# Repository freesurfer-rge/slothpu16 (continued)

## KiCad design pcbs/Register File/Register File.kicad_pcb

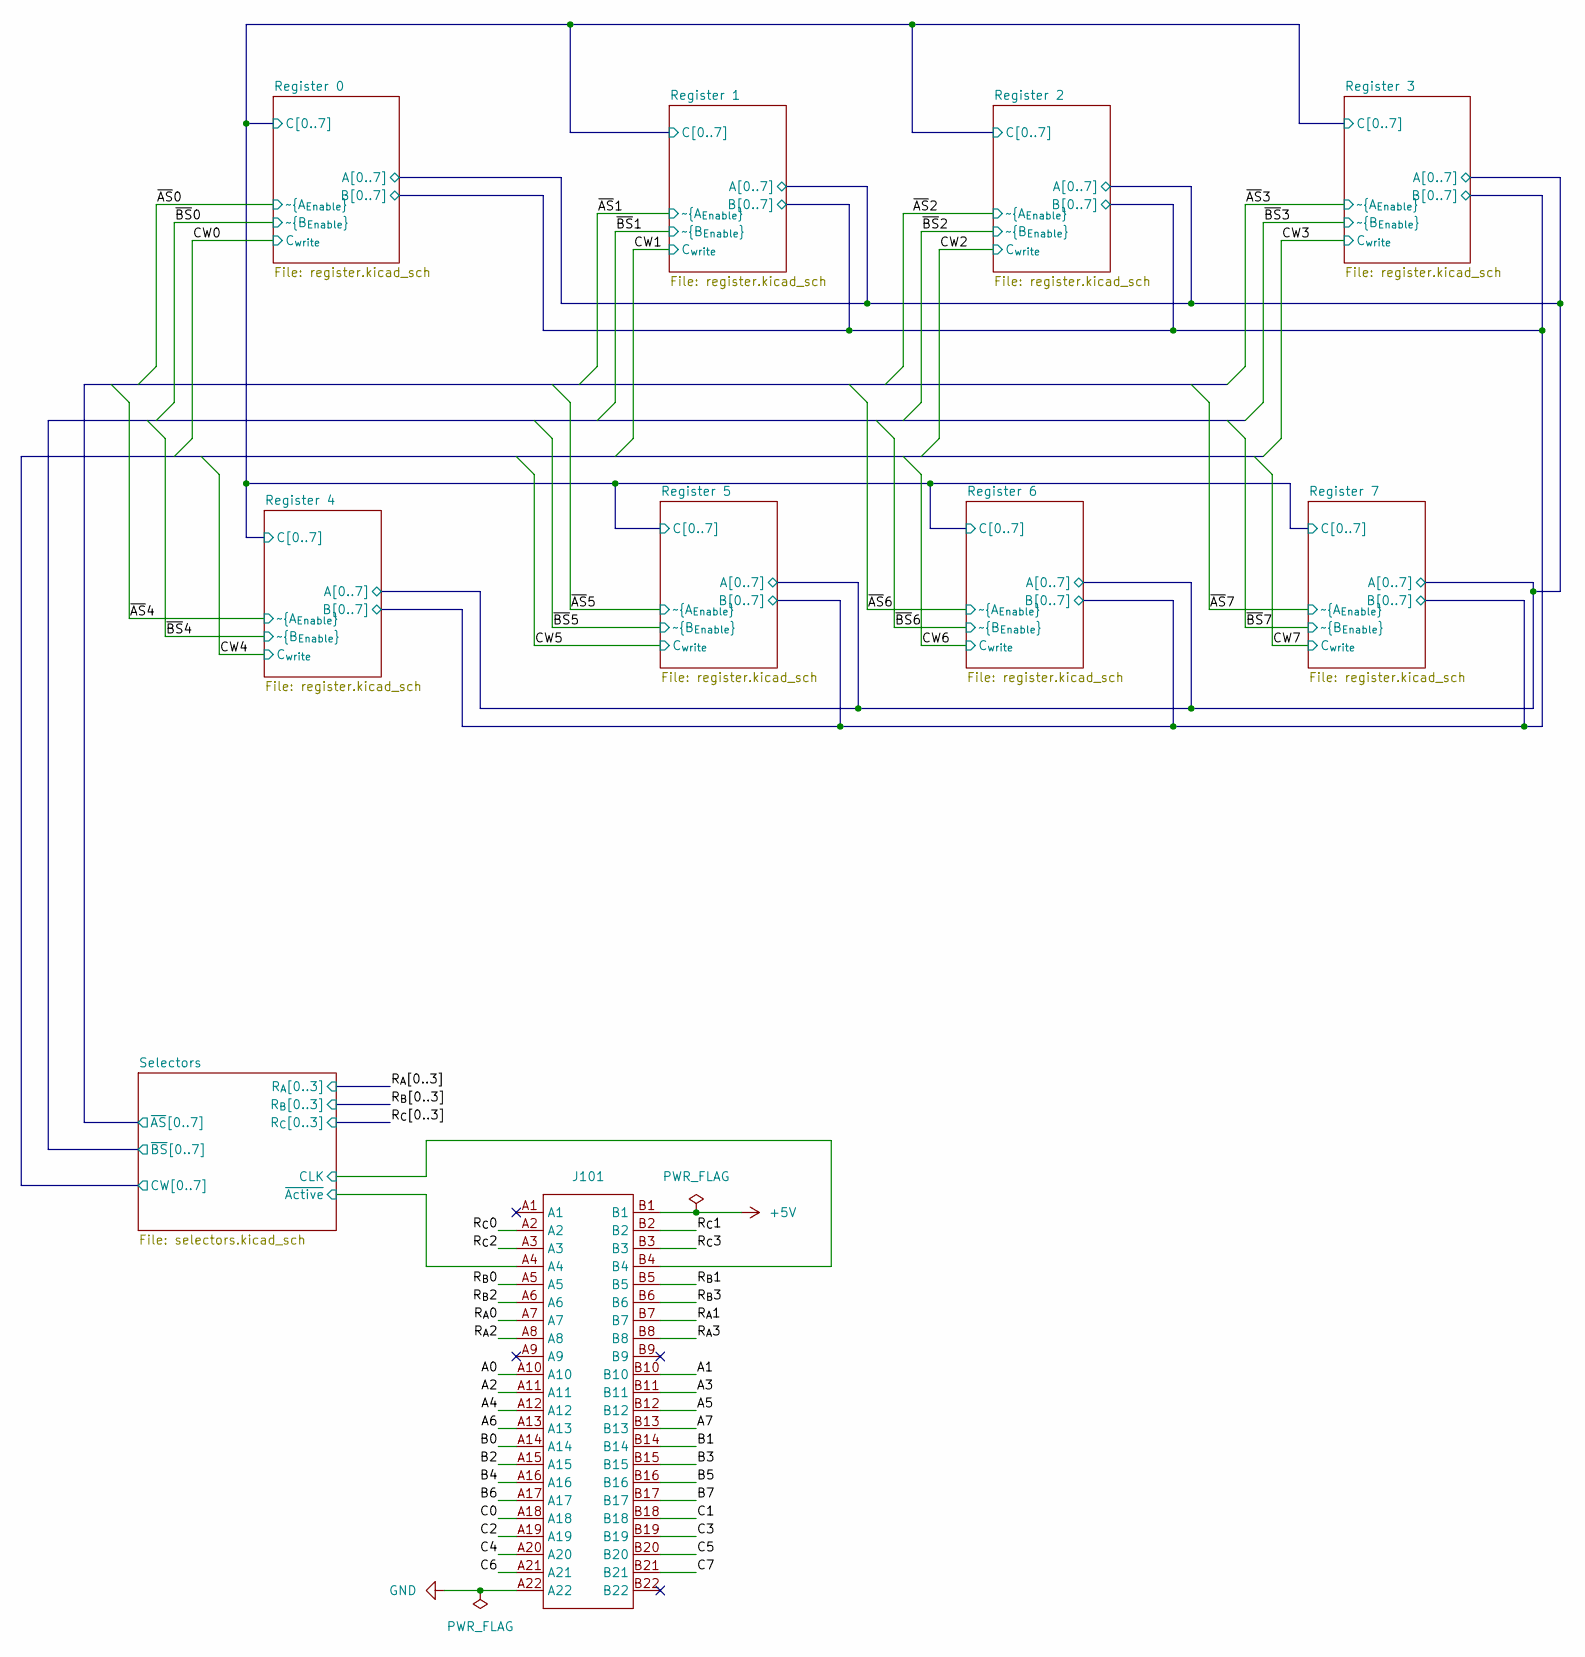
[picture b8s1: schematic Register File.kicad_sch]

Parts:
J101: TE-5530843-4-Edge

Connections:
+5V: J101.B1; also elsewhere on the board
/R_{A}0: J101.A7; also elsewhere on the board
/R_{A}1: J101.B7; also elsewhere on the board
/R_{A}2: J101.A8; also elsewhere on the board
/R_{A}3: J101.B8; also elsewhere on the board
/R_{B}0: J101.A5; also elsewhere on the board
/R_{B}1: J101.B5; also elsewhere on the board
/R_{B}2: J101.A6; also elsewhere on the board
/R_{B}3: J101.B6; also elsewhere on the board
/R_{C}0: J101.A2; also elsewhere on the board
/R_{C}1: J101.B2; also elsewhere on the board
/R_{C}2: J101.A3; also elsewhere on the board
/R_{C}3: J101.B3; also elsewhere on the board
/Register 0/A0: J101.A10; also elsewhere on the board
/Register 0/A1: J101.B10; also elsewhere on the board
/Register 0/A2: J101.A11; also elsewhere on the board
/Register 0/A3: J101.B11; also elsewhere on the board
/Register 0/A4: J101.A12; also elsewhere on the board
/Register 0/A5: J101.B12; also elsewhere on the board
/Register 0/A6: J101.A13; also elsewhere on the board
/Register 0/A7: J101.B13; also elsewhere on the board
/Register 0/B0: J101.A14; also elsewhere on the board
/Register 0/B1: J101.B14; also elsewhere on the board
/Register 0/B2: J101.A15; also elsewhere on the board
/Register 0/B3: J101.B15; also elsewhere on the board
/Register 0/B4: J101.A16; also elsewhere on the board
/Register 0/B5: J101.B16; also elsewhere on the board
/Register 0/B6: J101.A17; also elsewhere on the board
/Register 0/B7: J101.B17; also elsewhere on the board
/Register 0/C0: J101.A18; also elsewhere on the board
/Register 0/C1: J101.B18; also elsewhere on the board
/Register 0/C2: J101.A19; also elsewhere on the board
/Register 0/C3: J101.B19; also elsewhere on the board
/Register 0/C4: J101.A20; also elsewhere on the board
/Register 0/C5: J101.B20; also elsewhere on the board
/Register 0/C6: J101.A21; also elsewhere on the board
/Register 0/C7: J101.B21; also elsewhere on the board
/Selectors/CLK: J101.B4; also elsewhere on the board
/Selectors/~Active: J101.A4; also elsewhere on the board
GND: J101.A22; also elsewhere on the board

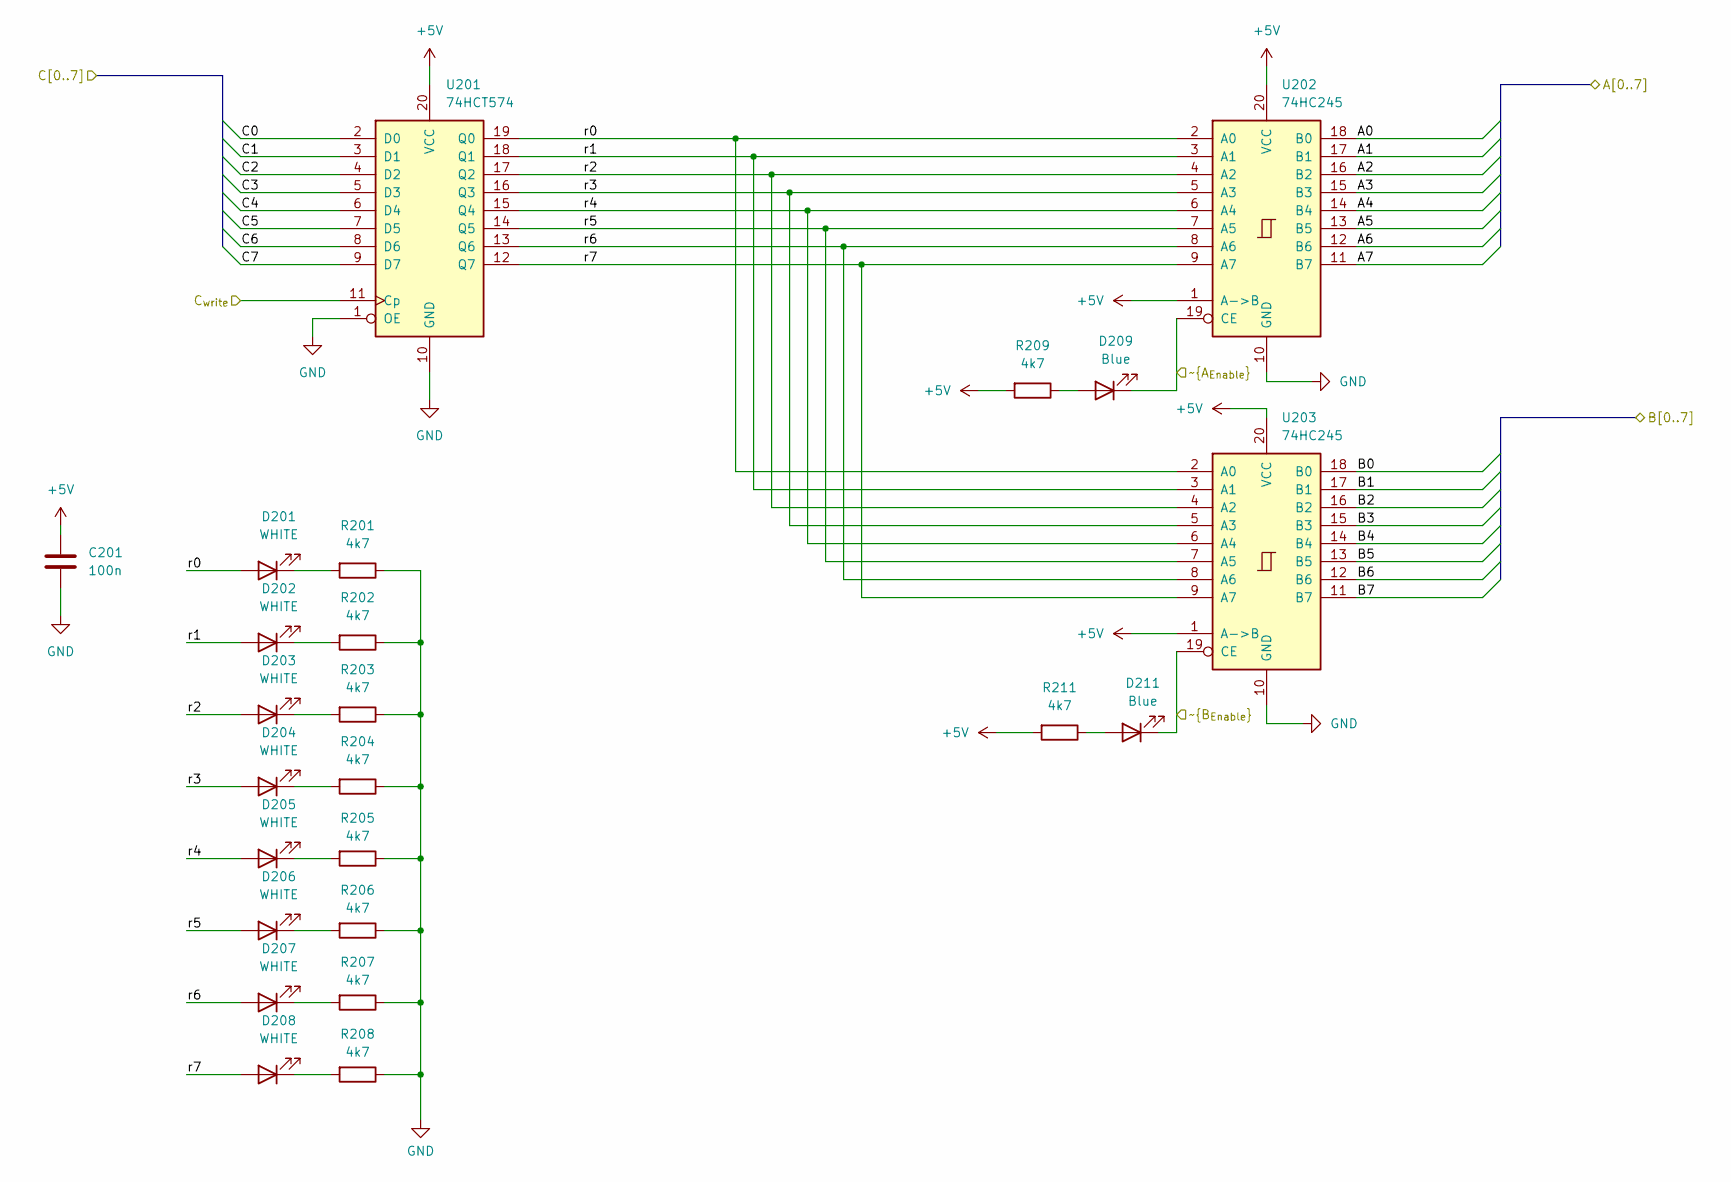
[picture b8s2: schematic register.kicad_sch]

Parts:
C201: 100n; C_0603_1608Metric; LCSC C14663
D201, D202, D203, D204, D205, D206, D207, D208: WHITE; LED_0603_1608Metric; LCSC C2290
D209, D211: Blue; LED_0603_1608Metric; LCSC C72041
R201, R202, R203, R204, R205, R206, R207, R208, R209, R211: 4k7; R_0603_1608Metric; LCSC C23162
U201: 74HCT574; DIP-20_W7.62mm_Socket
U202, U203: 74HC245; SOIC-20W_7.5x12.8mm_P1.27mm; LCSC C5625

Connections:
+5V: C201.1, R209.2, R211.2, U201.20 (VCC), U202.1 (A->B), U202.20 (VCC), U203.1 (A->B), U203.20 (VCC); also elsewhere on the board
/Register 0/A0: U202.18 (B0); also elsewhere on the board
/Register 0/A1: U202.17 (B1); also elsewhere on the board
/Register 0/A2: U202.16 (B2); also elsewhere on the board
/Register 0/A3: U202.15 (B3); also elsewhere on the board
/Register 0/A4: U202.14 (B4); also elsewhere on the board
/Register 0/A5: U202.13 (B5); also elsewhere on the board
/Register 0/A6: U202.12 (B6); also elsewhere on the board
/Register 0/A7: U202.11 (B7); also elsewhere on the board
/Register 0/B0: U203.18 (B0); also elsewhere on the board
/Register 0/B1: U203.17 (B1); also elsewhere on the board
/Register 0/B2: U203.16 (B2); also elsewhere on the board
/Register 0/B3: U203.15 (B3); also elsewhere on the board
/Register 0/B4: U203.14 (B4); also elsewhere on the board
/Register 0/B5: U203.13 (B5); also elsewhere on the board
/Register 0/B6: U203.12 (B6); also elsewhere on the board
/Register 0/B7: U203.11 (B7); also elsewhere on the board
/Register 0/C0: U201.2 (D0); also elsewhere on the board
/Register 0/C1: U201.3 (D1); also elsewhere on the board
/Register 0/C2: U201.4 (D2); also elsewhere on the board
/Register 0/C3: U201.5 (D3); also elsewhere on the board
/Register 0/C4: U201.6 (D4); also elsewhere on the board
/Register 0/C5: U201.7 (D5); also elsewhere on the board
/Register 0/C6: U201.8 (D6); also elsewhere on the board
/Register 0/C7: U201.9 (D7); also elsewhere on the board
/Register 0/r0: D201.2 (A), U201.19 (Q0), U202.2 (A0), U203.2 (A0)
/Register 0/r1: D202.2 (A), U201.18 (Q1), U202.3 (A1), U203.3 (A1)
/Register 0/r2: D203.2 (A), U201.17 (Q2), U202.4 (A2), U203.4 (A2)
/Register 0/r3: D204.2 (A), U201.16 (Q3), U202.5 (A3), U203.5 (A3)
/Register 0/r4: D205.2 (A), U201.15 (Q4), U202.6 (A4), U203.6 (A4)
/Register 0/r5: D206.2 (A), U201.14 (Q5), U202.7 (A5), U203.7 (A5)
/Register 0/r6: D207.2 (A), U201.13 (Q6), U202.8 (A6), U203.8 (A6)
/Register 0/r7: D208.2 (A), U201.12 (Q7), U202.9 (A7), U203.9 (A7)
/Selectors/CW0: U201.11 (Cp); also elsewhere on the board
/Selectors/~AS0: D209.1 (K), U202.19 (CE); also elsewhere on the board
/Selectors/~BS0: D211.1 (K), U203.19 (CE); also elsewhere on the board
GND: C201.2, R201.1, R202.1, R203.1, R204.1, R205.1, R206.1, R207.1, R208.1, U201.1 (OE), U201.10 (GND), U202.10 (GND), U203.10 (GND); also elsewhere on the board
unnamed: D201.1 (K), R201.2
unnamed: D202.1 (K), R202.2
unnamed: D203.1 (K), R203.2
unnamed: D204.1 (K), R204.2
unnamed: D205.1 (K), R205.2
unnamed: D206.1 (K), R206.2
unnamed: D207.1 (K), R207.2
unnamed: D208.1 (K), R208.2
unnamed: D209.2 (A), R209.1
unnamed: D211.2 (A), R211.1

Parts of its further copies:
C301, C401, C501, C601, C701, C801, C901: 100n; C_0603_1608Metric; LCSC C14663
D301, D302, D303, D304, D305, D306, D307, D308, D401, D402, D403, D404, D405, D406, D407, D408, D501, D502, D503, D504, D505, D506, D507, D508, D601, D602, D603, D604, D605, D606, D607, D608, D701, D702, D703, D704, D705, D706, D707, D708, D801, D802, D803, D804, D805, D806, D807, D808, D901, D902, D903, D904, D905, D906, D907, D908: WHITE; LED_0603_1608Metric; LCSC C2290
D309, D310, D409, D410, D509, D510, D609, D610, D709, D710, D809, D810, D909, D910: Blue; LED_0603_1608Metric; LCSC C72041
R301, R302, R303, R304, R305, R306, R307, R308, R309, R310, R401, R402, R403, R404, R405, R406, R407, R408, R409, R410, R501, R502, R503, R504, R505, R506, R507, R508, R509, R510, R601, R602, R603, R604, R605, R606, R607, R608, R609, R610, R701, R702, R703, R704, R705, R706, R707, R708, R709, R710, R801, R802, R803, R804, R805, R806, R807, R808, R809, R810, R901, R902, R903, R904, R905, R906, R907, R908, R909, R910: 4k7; R_0603_1608Metric; LCSC C23162
U301, U401, U501, U601, U701, U801, U901: 74HCT574; DIP-20_W7.62mm_Socket
U302, U303, U402, U403, U502, U503, U602, U603, U702, U703, U802, U803, U902, U903: 74HC245; SOIC-20W_7.5x12.8mm_P1.27mm; LCSC C5625

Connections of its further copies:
+5V: C301.1, C401.1, C501.1, C601.1, C701.1, C801.1, C901.1, R309.2, R310.2, R409.2, R410.2, R509.2, R510.2, R609.2, R610.2, R709.2, R710.2, R809.2, R810.2, R909.2, R910.2, U301.20 (VCC), U302.1 (A->B), U302.20 (VCC), U303.1 (A->B), U303.20 (VCC), U401.20 (VCC), U402.1 (A->B), U402.20 (VCC), U403.1 (A->B), U403.20 (VCC), U501.20 (VCC), U502.1 (A->B), U502.20 (VCC), U503.1 (A->B), U503.20 (VCC), U601.20 (VCC), U602.1 (A->B), U602.20 (VCC), U603.1 (A->B), U603.20 (VCC), U701.20 (VCC), U702.1 (A->B), U702.20 (VCC), U703.1 (A->B), U703.20 (VCC), U801.20 (VCC), U802.1 (A->B), U802.20 (VCC), U803.1 (A->B), U803.20 (VCC), U901.20 (VCC), U902.1 (A->B), U902.20 (VCC), U903.1 (A->B), U903.20 (VCC); also elsewhere on the board
/Register 0/A0: U302.18 (B0), U402.18 (B0), U502.18 (B0), U602.18 (B0), U702.18 (B0), U802.18 (B0), U902.18 (B0); also elsewhere on the board
/Register 0/A1: U302.17 (B1), U402.17 (B1), U502.17 (B1), U602.17 (B1), U702.17 (B1), U802.17 (B1), U902.17 (B1); also elsewhere on the board
/Register 0/A2: U302.16 (B2), U402.16 (B2), U502.16 (B2), U602.16 (B2), U702.16 (B2), U802.16 (B2), U902.16 (B2); also elsewhere on the board
/Register 0/A3: U302.15 (B3), U402.15 (B3), U502.15 (B3), U602.15 (B3), U702.15 (B3), U802.15 (B3), U902.15 (B3); also elsewhere on the board
/Register 0/A4: U302.14 (B4), U402.14 (B4), U502.14 (B4), U602.14 (B4), U702.14 (B4), U802.14 (B4), U902.14 (B4); also elsewhere on the board
/Register 0/A5: U302.13 (B5), U402.13 (B5), U502.13 (B5), U602.13 (B5), U702.13 (B5), U802.13 (B5), U902.13 (B5); also elsewhere on the board
/Register 0/A6: U302.12 (B6), U402.12 (B6), U502.12 (B6), U602.12 (B6), U702.12 (B6), U802.12 (B6), U902.12 (B6); also elsewhere on the board
/Register 0/A7: U302.11 (B7), U402.11 (B7), U502.11 (B7), U602.11 (B7), U702.11 (B7), U802.11 (B7), U902.11 (B7); also elsewhere on the board
/Register 0/B0: U303.18 (B0), U403.18 (B0), U503.18 (B0), U603.18 (B0), U703.18 (B0), U803.18 (B0), U903.18 (B0); also elsewhere on the board
/Register 0/B1: U303.17 (B1), U403.17 (B1), U503.17 (B1), U603.17 (B1), U703.17 (B1), U803.17 (B1), U903.17 (B1); also elsewhere on the board
/Register 0/B2: U303.16 (B2), U403.16 (B2), U503.16 (B2), U603.16 (B2), U703.16 (B2), U803.16 (B2), U903.16 (B2); also elsewhere on the board
/Register 0/B3: U303.15 (B3), U403.15 (B3), U503.15 (B3), U603.15 (B3), U703.15 (B3), U803.15 (B3), U903.15 (B3); also elsewhere on the board
/Register 0/B4: U303.14 (B4), U403.14 (B4), U503.14 (B4), U603.14 (B4), U703.14 (B4), U803.14 (B4), U903.14 (B4); also elsewhere on the board
/Register 0/B5: U303.13 (B5), U403.13 (B5), U503.13 (B5), U603.13 (B5), U703.13 (B5), U803.13 (B5), U903.13 (B5); also elsewhere on the board
/Register 0/B6: U303.12 (B6), U403.12 (B6), U503.12 (B6), U603.12 (B6), U703.12 (B6), U803.12 (B6), U903.12 (B6); also elsewhere on the board
/Register 0/B7: U303.11 (B7), U403.11 (B7), U503.11 (B7), U603.11 (B7), U703.11 (B7), U803.11 (B7), U903.11 (B7); also elsewhere on the board
/Register 0/C0: U301.2 (D0), U401.2 (D0), U501.2 (D0), U601.2 (D0), U701.2 (D0), U801.2 (D0), U901.2 (D0); also elsewhere on the board
/Register 0/C1: U301.3 (D1), U401.3 (D1), U501.3 (D1), U601.3 (D1), U701.3 (D1), U801.3 (D1), U901.3 (D1); also elsewhere on the board
/Register 0/C2: U301.4 (D2), U401.4 (D2), U501.4 (D2), U601.4 (D2), U701.4 (D2), U801.4 (D2), U901.4 (D2); also elsewhere on the board
/Register 0/C3: U301.5 (D3), U401.5 (D3), U501.5 (D3), U601.5 (D3), U701.5 (D3), U801.5 (D3), U901.5 (D3); also elsewhere on the board
/Register 0/C4: U301.6 (D4), U401.6 (D4), U501.6 (D4), U601.6 (D4), U701.6 (D4), U801.6 (D4), U901.6 (D4); also elsewhere on the board
/Register 0/C5: U301.7 (D5), U401.7 (D5), U501.7 (D5), U601.7 (D5), U701.7 (D5), U801.7 (D5), U901.7 (D5); also elsewhere on the board
/Register 0/C6: U301.8 (D6), U401.8 (D6), U501.8 (D6), U601.8 (D6), U701.8 (D6), U801.8 (D6), U901.8 (D6); also elsewhere on the board
/Register 0/C7: U301.9 (D7), U401.9 (D7), U501.9 (D7), U601.9 (D7), U701.9 (D7), U801.9 (D7), U901.9 (D7); also elsewhere on the board
/Register 1/r0: D301.2 (A), U301.19 (Q0), U302.2 (A0), U303.2 (A0)
/Register 1/r1: D302.2 (A), U301.18 (Q1), U302.3 (A1), U303.3 (A1)
/Register 1/r2: D303.2 (A), U301.17 (Q2), U302.4 (A2), U303.4 (A2)
/Register 1/r3: D304.2 (A), U301.16 (Q3), U302.5 (A3), U303.5 (A3)
/Register 1/r4: D305.2 (A), U301.15 (Q4), U302.6 (A4), U303.6 (A4)
/Register 1/r5: D306.2 (A), U301.14 (Q5), U302.7 (A5), U303.7 (A5)
/Register 1/r6: D307.2 (A), U301.13 (Q6), U302.8 (A6), U303.8 (A6)
/Register 1/r7: D308.2 (A), U301.12 (Q7), U302.9 (A7), U303.9 (A7)
/Register 2/r0: D401.2 (A), U401.19 (Q0), U402.2 (A0), U403.2 (A0)
/Register 2/r1: D402.2 (A), U401.18 (Q1), U402.3 (A1), U403.3 (A1)
/Register 2/r2: D403.2 (A), U401.17 (Q2), U402.4 (A2), U403.4 (A2)
/Register 2/r3: D404.2 (A), U401.16 (Q3), U402.5 (A3), U403.5 (A3)
/Register 2/r4: D405.2 (A), U401.15 (Q4), U402.6 (A4), U403.6 (A4)
/Register 2/r5: D406.2 (A), U401.14 (Q5), U402.7 (A5), U403.7 (A5)
/Register 2/r6: D407.2 (A), U401.13 (Q6), U402.8 (A6), U403.8 (A6)
/Register 2/r7: D408.2 (A), U401.12 (Q7), U402.9 (A7), U403.9 (A7)
/Register 3/r0: D501.2 (A), U501.19 (Q0), U502.2 (A0), U503.2 (A0)
/Register 3/r1: D502.2 (A), U501.18 (Q1), U502.3 (A1), U503.3 (A1)
/Register 3/r2: D503.2 (A), U501.17 (Q2), U502.4 (A2), U503.4 (A2)
/Register 3/r3: D504.2 (A), U501.16 (Q3), U502.5 (A3), U503.5 (A3)
/Register 3/r4: D505.2 (A), U501.15 (Q4), U502.6 (A4), U503.6 (A4)
/Register 3/r5: D506.2 (A), U501.14 (Q5), U502.7 (A5), U503.7 (A5)
/Register 3/r6: D507.2 (A), U501.13 (Q6), U502.8 (A6), U503.8 (A6)
/Register 3/r7: D508.2 (A), U501.12 (Q7), U502.9 (A7), U503.9 (A7)
/Register 4/r0: D601.2 (A), U601.19 (Q0), U602.2 (A0), U603.2 (A0)
/Register 4/r1: D602.2 (A), U601.18 (Q1), U602.3 (A1), U603.3 (A1)
/Register 4/r2: D603.2 (A), U601.17 (Q2), U602.4 (A2), U603.4 (A2)
/Register 4/r3: D604.2 (A), U601.16 (Q3), U602.5 (A3), U603.5 (A3)
/Register 4/r4: D605.2 (A), U601.15 (Q4), U602.6 (A4), U603.6 (A4)
/Register 4/r5: D606.2 (A), U601.14 (Q5), U602.7 (A5), U603.7 (A5)
/Register 4/r6: D607.2 (A), U601.13 (Q6), U602.8 (A6), U603.8 (A6)
/Register 4/r7: D608.2 (A), U601.12 (Q7), U602.9 (A7), U603.9 (A7)
/Register 5/r0: D701.2 (A), U701.19 (Q0), U702.2 (A0), U703.2 (A0)
/Register 5/r1: D702.2 (A), U701.18 (Q1), U702.3 (A1), U703.3 (A1)
/Register 5/r2: D703.2 (A), U701.17 (Q2), U702.4 (A2), U703.4 (A2)
/Register 5/r3: D704.2 (A), U701.16 (Q3), U702.5 (A3), U703.5 (A3)
/Register 5/r4: D705.2 (A), U701.15 (Q4), U702.6 (A4), U703.6 (A4)
/Register 5/r5: D706.2 (A), U701.14 (Q5), U702.7 (A5), U703.7 (A5)
/Register 5/r6: D707.2 (A), U701.13 (Q6), U702.8 (A6), U703.8 (A6)
/Register 5/r7: D708.2 (A), U701.12 (Q7), U702.9 (A7), U703.9 (A7)
/Register 6/r0: D801.2 (A), U801.19 (Q0), U802.2 (A0), U803.2 (A0)
/Register 6/r1: D802.2 (A), U801.18 (Q1), U802.3 (A1), U803.3 (A1)
/Register 6/r2: D803.2 (A), U801.17 (Q2), U802.4 (A2), U803.4 (A2)
/Register 6/r3: D804.2 (A), U801.16 (Q3), U802.5 (A3), U803.5 (A3)
/Register 6/r4: D805.2 (A), U801.15 (Q4), U802.6 (A4), U803.6 (A4)
/Register 6/r5: D806.2 (A), U801.14 (Q5), U802.7 (A5), U803.7 (A5)
/Register 6/r6: D807.2 (A), U801.13 (Q6), U802.8 (A6), U803.8 (A6)
/Register 6/r7: D808.2 (A), U801.12 (Q7), U802.9 (A7), U803.9 (A7)
/Register 7/r0: D901.2 (A), U901.19 (Q0), U902.2 (A0), U903.2 (A0)
/Register 7/r1: D902.2 (A), U901.18 (Q1), U902.3 (A1), U903.3 (A1)
/Register 7/r2: D903.2 (A), U901.17 (Q2), U902.4 (A2), U903.4 (A2)
/Register 7/r3: D904.2 (A), U901.16 (Q3), U902.5 (A3), U903.5 (A3)
/Register 7/r4: D905.2 (A), U901.15 (Q4), U902.6 (A4), U903.6 (A4)
/Register 7/r5: D906.2 (A), U901.14 (Q5), U902.7 (A5), U903.7 (A5)
/Register 7/r6: D907.2 (A), U901.13 (Q6), U902.8 (A6), U903.8 (A6)
/Register 7/r7: D908.2 (A), U901.12 (Q7), U902.9 (A7), U903.9 (A7)
/Selectors/CW1: U301.11 (Cp); also elsewhere on the board
/Selectors/CW2: U401.11 (Cp); also elsewhere on the board
/Selectors/CW3: U501.11 (Cp); also elsewhere on the board
/Selectors/CW4: U601.11 (Cp); also elsewhere on the board
/Selectors/CW5: U701.11 (Cp); also elsewhere on the board
/Selectors/CW6: U801.11 (Cp); also elsewhere on the board
/Selectors/CW7: U901.11 (Cp); also elsewhere on the board
/Selectors/~AS1: D309.1 (K), U302.19 (CE); also elsewhere on the board
/Selectors/~AS2: D409.1 (K), U402.19 (CE); also elsewhere on the board
/Selectors/~AS3: D509.1 (K), U502.19 (CE); also elsewhere on the board
/Selectors/~AS4: D609.1 (K), U602.19 (CE); also elsewhere on the board
/Selectors/~AS5: D709.1 (K), U702.19 (CE); also elsewhere on the board
/Selectors/~AS6: D809.1 (K), U802.19 (CE); also elsewhere on the board
/Selectors/~AS7: D909.1 (K), U902.19 (CE); also elsewhere on the board
/Selectors/~BS1: D310.1 (K), U303.19 (CE); also elsewhere on the board
/Selectors/~BS2: D410.1 (K), U403.19 (CE); also elsewhere on the board
/Selectors/~BS3: D510.1 (K), U503.19 (CE); also elsewhere on the board
/Selectors/~BS4: D610.1 (K), U603.19 (CE); also elsewhere on the board
/Selectors/~BS5: D710.1 (K), U703.19 (CE); also elsewhere on the board
/Selectors/~BS6: D810.1 (K), U803.19 (CE); also elsewhere on the board
/Selectors/~BS7: D910.1 (K), U903.19 (CE); also elsewhere on the board
GND: C301.2, C401.2, C501.2, C601.2, C701.2, C801.2, C901.2, R301.1, R302.1, R303.1, R304.1, R305.1, R306.1, R307.1, R308.1, R401.1, R402.1, R403.1, R404.1, R405.1, R406.1, R407.1, R408.1, R501.1, R502.1, R503.1, R504.1, R505.1, R506.1, R507.1, R508.1, R601.1, R602.1, R603.1, R604.1, R605.1, R606.1, R607.1, R608.1, R701.1, R702.1, R703.1, R704.1, R705.1, R706.1, R707.1, R708.1, R801.1, R802.1, R803.1, R804.1, R805.1, R806.1, R807.1, R808.1, R901.1, R902.1, R903.1, R904.1, R905.1, R906.1, R907.1, R908.1, U301.1 (OE), U301.10 (GND), U302.10 (GND), U303.10 (GND), U401.1 (OE), U401.10 (GND), U402.10 (GND), U403.10 (GND), U501.1 (OE), U501.10 (GND), U502.10 (GND), U503.10 (GND), U601.1 (OE), U601.10 (GND), U602.10 (GND), U603.10 (GND), U701.1 (OE), U701.10 (GND), U702.10 (GND), U703.10 (GND), U801.1 (OE), U801.10 (GND), U802.10 (GND), U803.10 (GND), U901.1 (OE), U901.10 (GND), U902.10 (GND), U903.10 (GND); also elsewhere on the board
unnamed: D301.1 (K), R301.2
unnamed: D302.1 (K), R302.2
unnamed: D303.1 (K), R303.2
unnamed: D304.1 (K), R304.2
unnamed: D305.1 (K), R305.2
unnamed: D306.1 (K), R306.2
unnamed: D307.1 (K), R307.2
unnamed: D308.1 (K), R308.2
unnamed: D309.2 (A), R309.1
unnamed: D310.2 (A), R310.1
unnamed: D401.1 (K), R401.2
unnamed: D402.1 (K), R402.2
unnamed: D403.1 (K), R403.2
unnamed: D404.1 (K), R404.2
unnamed: D405.1 (K), R405.2
unnamed: D406.1 (K), R406.2
unnamed: D407.1 (K), R407.2
unnamed: D408.1 (K), R408.2
unnamed: D409.2 (A), R409.1
unnamed: D410.2 (A), R410.1
unnamed: D501.1 (K), R501.2
unnamed: D502.1 (K), R502.2
unnamed: D503.1 (K), R503.2
unnamed: D504.1 (K), R504.2
unnamed: D505.1 (K), R505.2
unnamed: D506.1 (K), R506.2
unnamed: D507.1 (K), R507.2
unnamed: D508.1 (K), R508.2
unnamed: D509.2 (A), R509.1
unnamed: D510.2 (A), R510.1
unnamed: D601.1 (K), R601.2
unnamed: D602.1 (K), R602.2
unnamed: D603.1 (K), R603.2
unnamed: D604.1 (K), R604.2
unnamed: D605.1 (K), R605.2
unnamed: D606.1 (K), R606.2
unnamed: D607.1 (K), R607.2
unnamed: D608.1 (K), R608.2
unnamed: D609.2 (A), R609.1
unnamed: D610.2 (A), R610.1
unnamed: D701.1 (K), R701.2
unnamed: D702.1 (K), R702.2
unnamed: D703.1 (K), R703.2
unnamed: D704.1 (K), R704.2
unnamed: D705.1 (K), R705.2
unnamed: D706.1 (K), R706.2
unnamed: D707.1 (K), R707.2
unnamed: D708.1 (K), R708.2
unnamed: D709.2 (A), R709.1
unnamed: D710.2 (A), R710.1
unnamed: D801.1 (K), R801.2
unnamed: D802.1 (K), R802.2
unnamed: D803.1 (K), R803.2
unnamed: D804.1 (K), R804.2
unnamed: D805.1 (K), R805.2
unnamed: D806.1 (K), R806.2
unnamed: D807.1 (K), R807.2
unnamed: D808.1 (K), R808.2
unnamed: D809.2 (A), R809.1
unnamed: D810.2 (A), R810.1
unnamed: D901.1 (K), R901.2
unnamed: D902.1 (K), R902.2
unnamed: D903.1 (K), R903.2
unnamed: D904.1 (K), R904.2
unnamed: D905.1 (K), R905.2
unnamed: D906.1 (K), R906.2
unnamed: D907.1 (K), R907.2
unnamed: D908.1 (K), R908.2
unnamed: D909.2 (A), R909.1
unnamed: D910.2 (A), R910.1

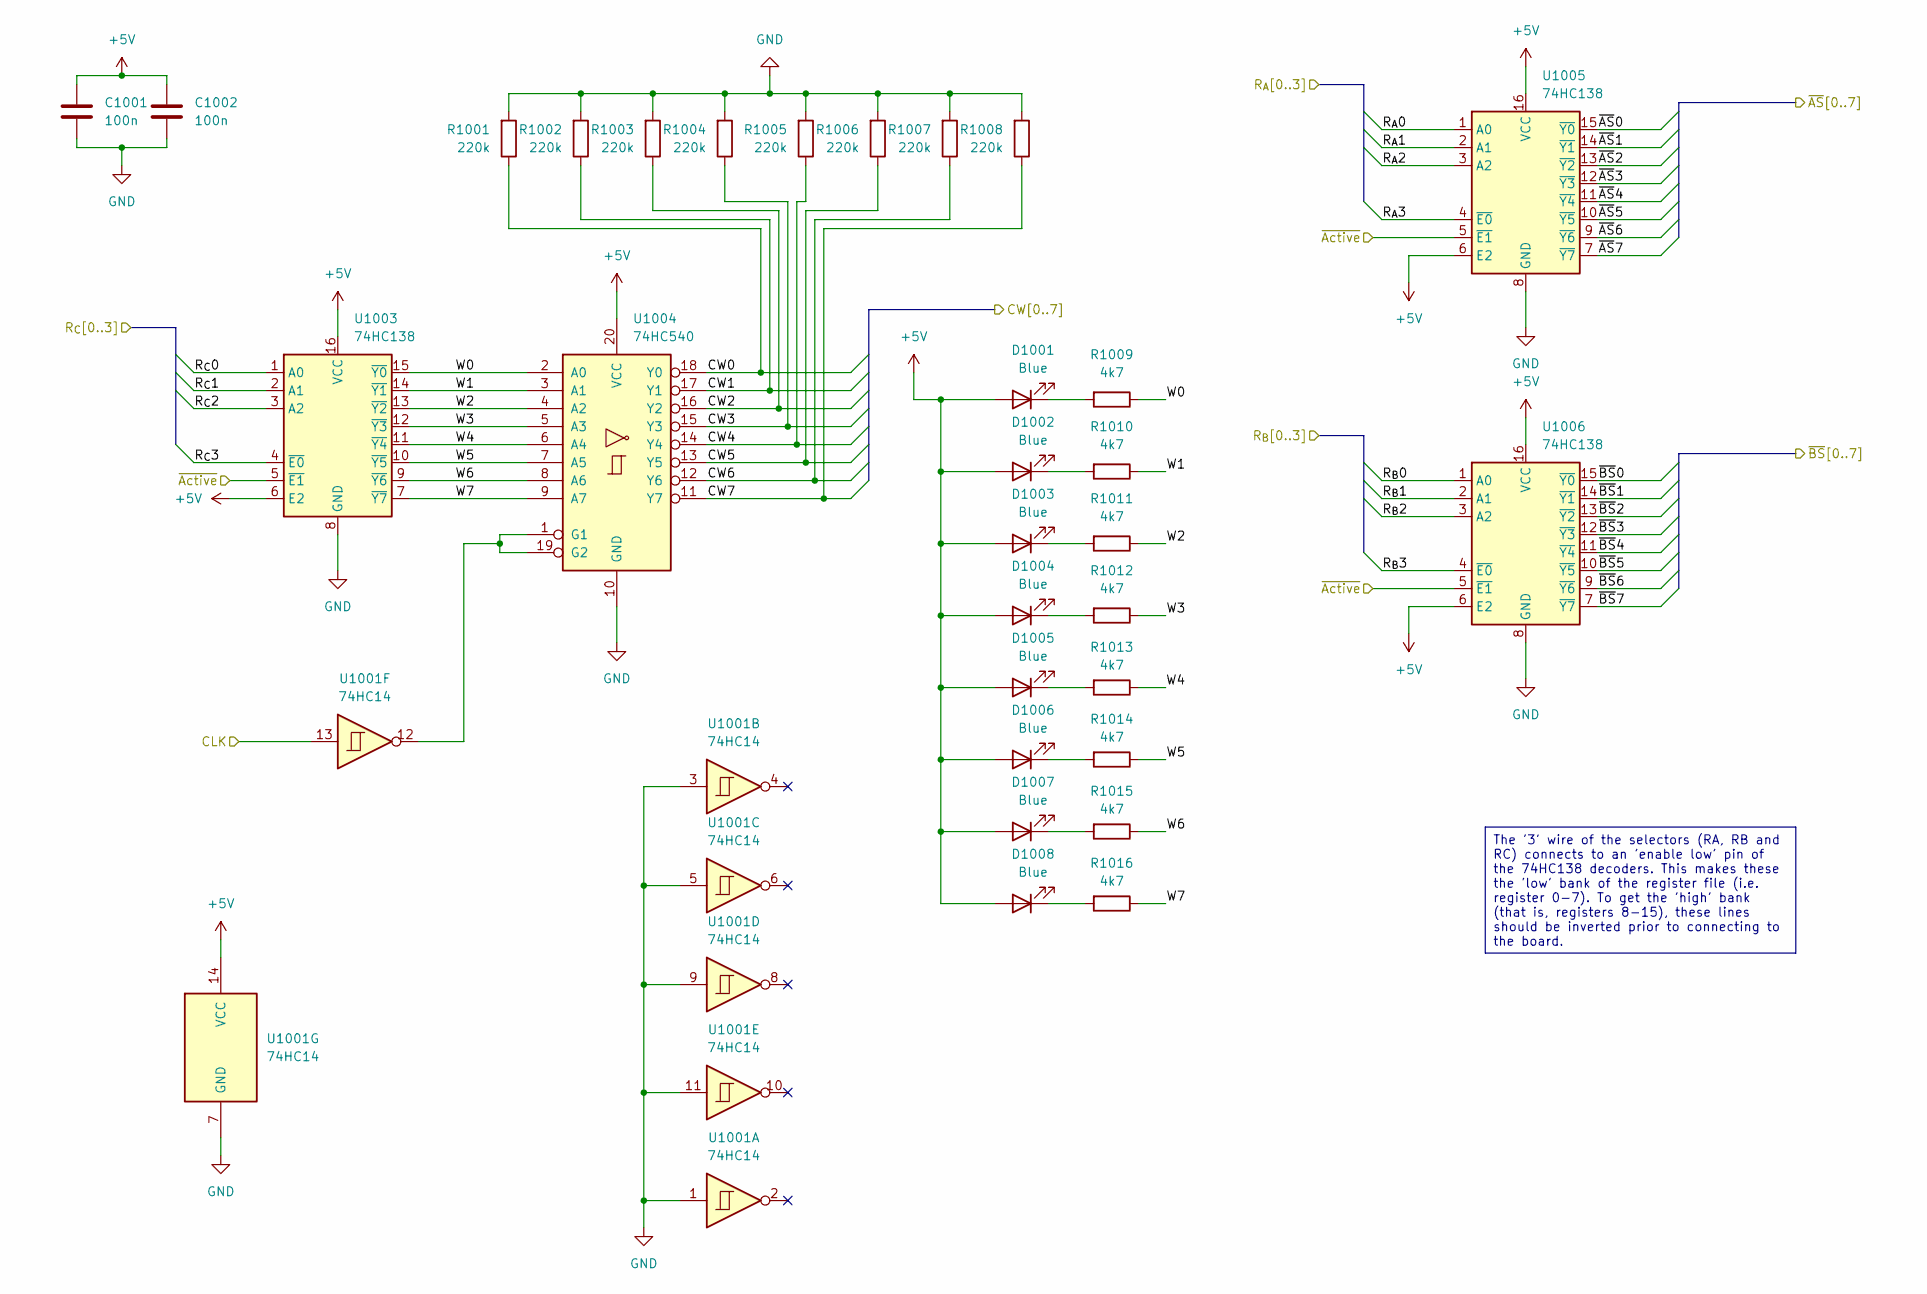
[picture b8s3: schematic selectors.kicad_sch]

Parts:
C1001, C1002: 100n; C_0603_1608Metric; LCSC C14663
D1001, D1002, D1003, D1004, D1005, D1006, D1007, D1008: Blue; LED_0603_1608Metric; LCSC C72041
R1001, R1002, R1003, R1004, R1005, R1006, R1007, R1008: 220k; R_0603_1608Metric; LCSC C22961
R1009, R1010, R1011, R1012, R1013, R1014, R1015, R1016: 4k7; R_0603_1608Metric; LCSC C23162
U1001: 74HC14; SOIC-14_3.9x8.7mm_P1.27mm; LCSC C5605
U1003, U1005, U1006: 74HC138; DIP-16_W7.62mm_Socket
U1004: 74HC540; DIP-20_W7.62mm_Socket

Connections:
+5V: C1001.1, C1002.1, D1001.2 (A), D1002.2 (A), D1003.2 (A), D1004.2 (A), D1005.2 (A), D1006.2 (A), D1007.2 (A), D1008.2 (A), U1001.14 (VCC), U1003.6 (E2), U1003.16 (VCC), U1004.20 (VCC), U1005.6 (E2), U1005.16 (VCC), U1006.6 (E2), U1006.16 (VCC); also elsewhere on the board
/R_{A}0: U1005.1 (A0); also elsewhere on the board
/R_{A}1: U1005.2 (A1); also elsewhere on the board
/R_{A}2: U1005.3 (A2); also elsewhere on the board
/R_{A}3: U1005.4 (~E0); also elsewhere on the board
/R_{B}0: U1006.1 (A0); also elsewhere on the board
/R_{B}1: U1006.2 (A1); also elsewhere on the board
/R_{B}2: U1006.3 (A2); also elsewhere on the board
/R_{B}3: U1006.4 (~E0); also elsewhere on the board
/R_{C}0: U1003.1 (A0); also elsewhere on the board
/R_{C}1: U1003.2 (A1); also elsewhere on the board
/R_{C}2: U1003.3 (A2); also elsewhere on the board
/R_{C}3: U1003.4 (~E0); also elsewhere on the board
/Selectors/CLK: U1001.13; also elsewhere on the board
/Selectors/CW0: R1001.1, U1004.18 (Y0); also elsewhere on the board
/Selectors/CW1: R1002.1, U1004.17 (Y1); also elsewhere on the board
/Selectors/CW2: R1003.1, U1004.16 (Y2); also elsewhere on the board
/Selectors/CW3: R1004.1, U1004.15 (Y3); also elsewhere on the board
/Selectors/CW4: R1005.1, U1004.14 (Y4); also elsewhere on the board
/Selectors/CW5: R1006.1, U1004.13 (Y5); also elsewhere on the board
/Selectors/CW6: R1007.1, U1004.12 (Y6); also elsewhere on the board
/Selectors/CW7: R1008.1, U1004.11 (Y7); also elsewhere on the board
/Selectors/W0: R1009.1, U1003.15 (~Y0), U1004.2 (A0)
/Selectors/W1: R1010.1, U1003.14 (~Y1), U1004.3 (A1)
/Selectors/W2: R1011.1, U1003.13 (~Y2), U1004.4 (A2)
/Selectors/W3: R1012.1, U1003.12 (~Y3), U1004.5 (A3)
/Selectors/W4: R1013.1, U1003.11 (~Y4), U1004.6 (A4)
/Selectors/W5: R1014.1, U1003.10 (~Y5), U1004.7 (A5)
/Selectors/W6: R1015.1, U1003.9 (~Y6), U1004.8 (A6)
/Selectors/W7: R1016.1, U1003.7 (~Y7), U1004.9 (A7)
/Selectors/~AS0: U1005.15 (~Y0); also elsewhere on the board
/Selectors/~AS1: U1005.14 (~Y1); also elsewhere on the board
/Selectors/~AS2: U1005.13 (~Y2); also elsewhere on the board
/Selectors/~AS3: U1005.12 (~Y3); also elsewhere on the board
/Selectors/~AS4: U1005.11 (~Y4); also elsewhere on the board
/Selectors/~AS5: U1005.10 (~Y5); also elsewhere on the board
/Selectors/~AS6: U1005.9 (~Y6); also elsewhere on the board
/Selectors/~AS7: U1005.7 (~Y7); also elsewhere on the board
/Selectors/~Active: U1003.5 (~E1), U1005.5 (~E1), U1006.5 (~E1); also elsewhere on the board
/Selectors/~BS0: U1006.15 (~Y0); also elsewhere on the board
/Selectors/~BS1: U1006.14 (~Y1); also elsewhere on the board
/Selectors/~BS2: U1006.13 (~Y2); also elsewhere on the board
/Selectors/~BS3: U1006.12 (~Y3); also elsewhere on the board
/Selectors/~BS4: U1006.11 (~Y4); also elsewhere on the board
/Selectors/~BS5: U1006.10 (~Y5); also elsewhere on the board
/Selectors/~BS6: U1006.9 (~Y6); also elsewhere on the board
/Selectors/~BS7: U1006.7 (~Y7); also elsewhere on the board
GND: C1001.2, C1002.2, R1001.2, R1002.2, R1003.2, R1004.2, R1005.2, R1006.2, R1007.2, R1008.2, U1001.1, U1001.3, U1001.5, U1001.7 (GND), U1001.9, U1001.11, U1003.8 (GND), U1004.10 (GND), U1005.8 (GND), U1006.8 (GND); also elsewhere on the board
unnamed: D1001.1 (K), R1009.2
unnamed: D1002.1 (K), R1010.2
unnamed: D1003.1 (K), R1011.2
unnamed: D1004.1 (K), R1012.2
unnamed: D1005.1 (K), R1013.2
unnamed: D1006.1 (K), R1014.2
unnamed: D1007.1 (K), R1015.2
unnamed: D1008.1 (K), R1016.2
unnamed: U1001.12, U1004.1 (G1), U1004.19 (G2)

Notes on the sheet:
The '3' wire of the selectors (RA, RB and RC) connects to an 'enable low' pin of the 74HC138 decoders. This makes these the 'low' bank of the register file (i.e. register 0-7). To get the 'high' bank (that is, registers 8-15), these lines should be inverted prior to connecting to the board.

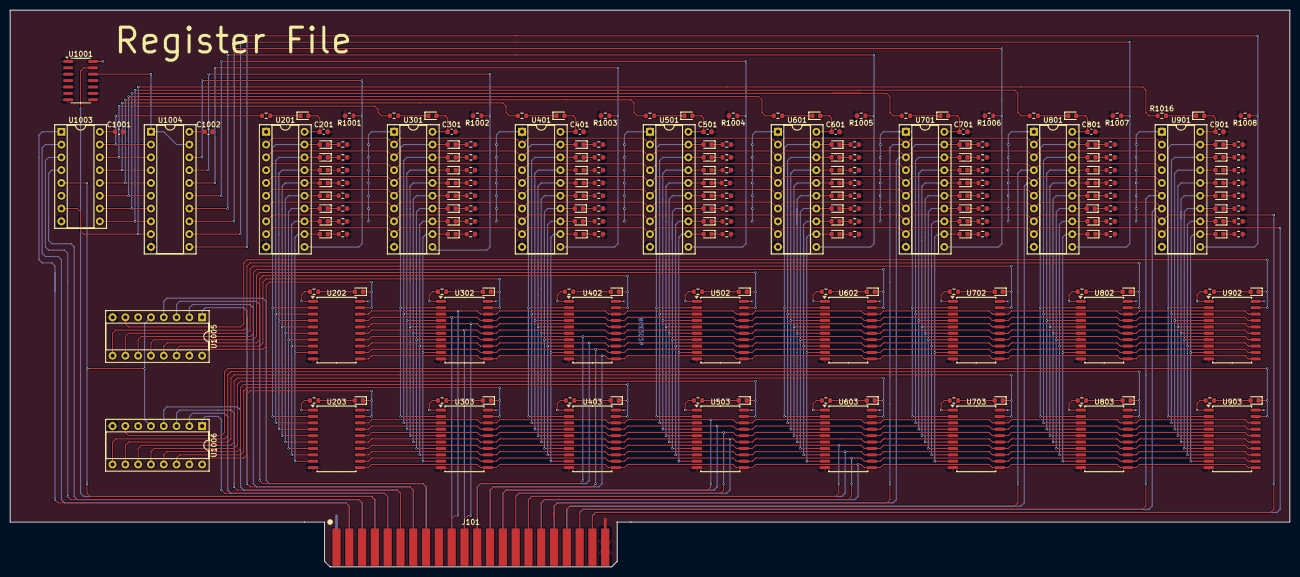
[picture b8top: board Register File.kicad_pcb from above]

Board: 2 copper layers, 254.0 x 110.5 mm, 224 parts (0 on the bottom side), 225 nets.
